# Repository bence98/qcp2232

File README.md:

# QCP2232HV USB-to-Quad UART

## Features

4 TTL UARTs with full Flow Control
* Tx, Rx full duplex
* RTS/CTS (Request-/Clear-to-Send), DTR/DSR (Data Terminal/Set Ready)
* DCD (Data Carrier Detect), RI (Ring Indicator) inputs
* all pins ESD protected
  * full TVS diode protection
  * overcurrent limiting resistors
* see pinout at the end of the section

UART0 and UART1 have RS-232 option
* only Tx/Rx
* separate industrial connector
  * Phoenix MCV 1,5 G-3.81
  * Würth WR-TBL 321

UART3 has selectable TTL voltage (`Vsel`)
* 5V from USB or 3.3V from internal regulator
* UART0-2 are 3.3V

USB Type-B connector
* superior mechanical stability compared to Micro-B
* easier to handle than Mini-B
* more economical to produce than Type-C
* added noise immunity thanks to EMI suppression circuitry
* supports USB suspend mode

16 GPIOs
* 3.3V digital I/O
* all pins ESD protected
  * full TVS diode protection
  * overcurrent limiting resistors
* alternate functions, see table below
  * Tx, Rx LED: blinks on data transfer
  * Tx mode: for half duplex bus drivers eg. RS-485
  * clock: USART bit clock
* configurable via Silicon Labs' toolchain

| GPIO # | UART # | function |
|--------|--------|----------|
|      0 |      0 |   Tx LED |
|      1 |      0 |   Rx LED |
|      2 |      0 |  Tx mode |
|      3 |      0 |    clock |
|      4 |      1 |   Tx LED |
|      5 |      1 |   Rx LED |
|      6 |      1 |  Tx mode |
|      7 |      1 |    clock |
|      8 |      2 |   Tx LED |
|      9 |      2 |   Rx LED |
|     10 |      2 |  Tx mode |
|     11 |      2 |    clock |
|     12 |      3 |   Tx LED |
|     13 |      3 |   Rx LED |
|     14 |      3 |  Tx mode |
|     15 |      3 |    clock |

Pinout (UARTs):

|                | GND | TX  | RX | RTS | CTS | DTR | DSR | DCD | RI |
|----------------|-----|-----|----|-----|-----|-----|-----|-----|----|
| Label on board |     | Tx  | Rx | RS  | CS  | DT  | DS  | CD  | RI |
| Direction      | N/A | Out | In | Out | In  | Out | In  | In  | In |

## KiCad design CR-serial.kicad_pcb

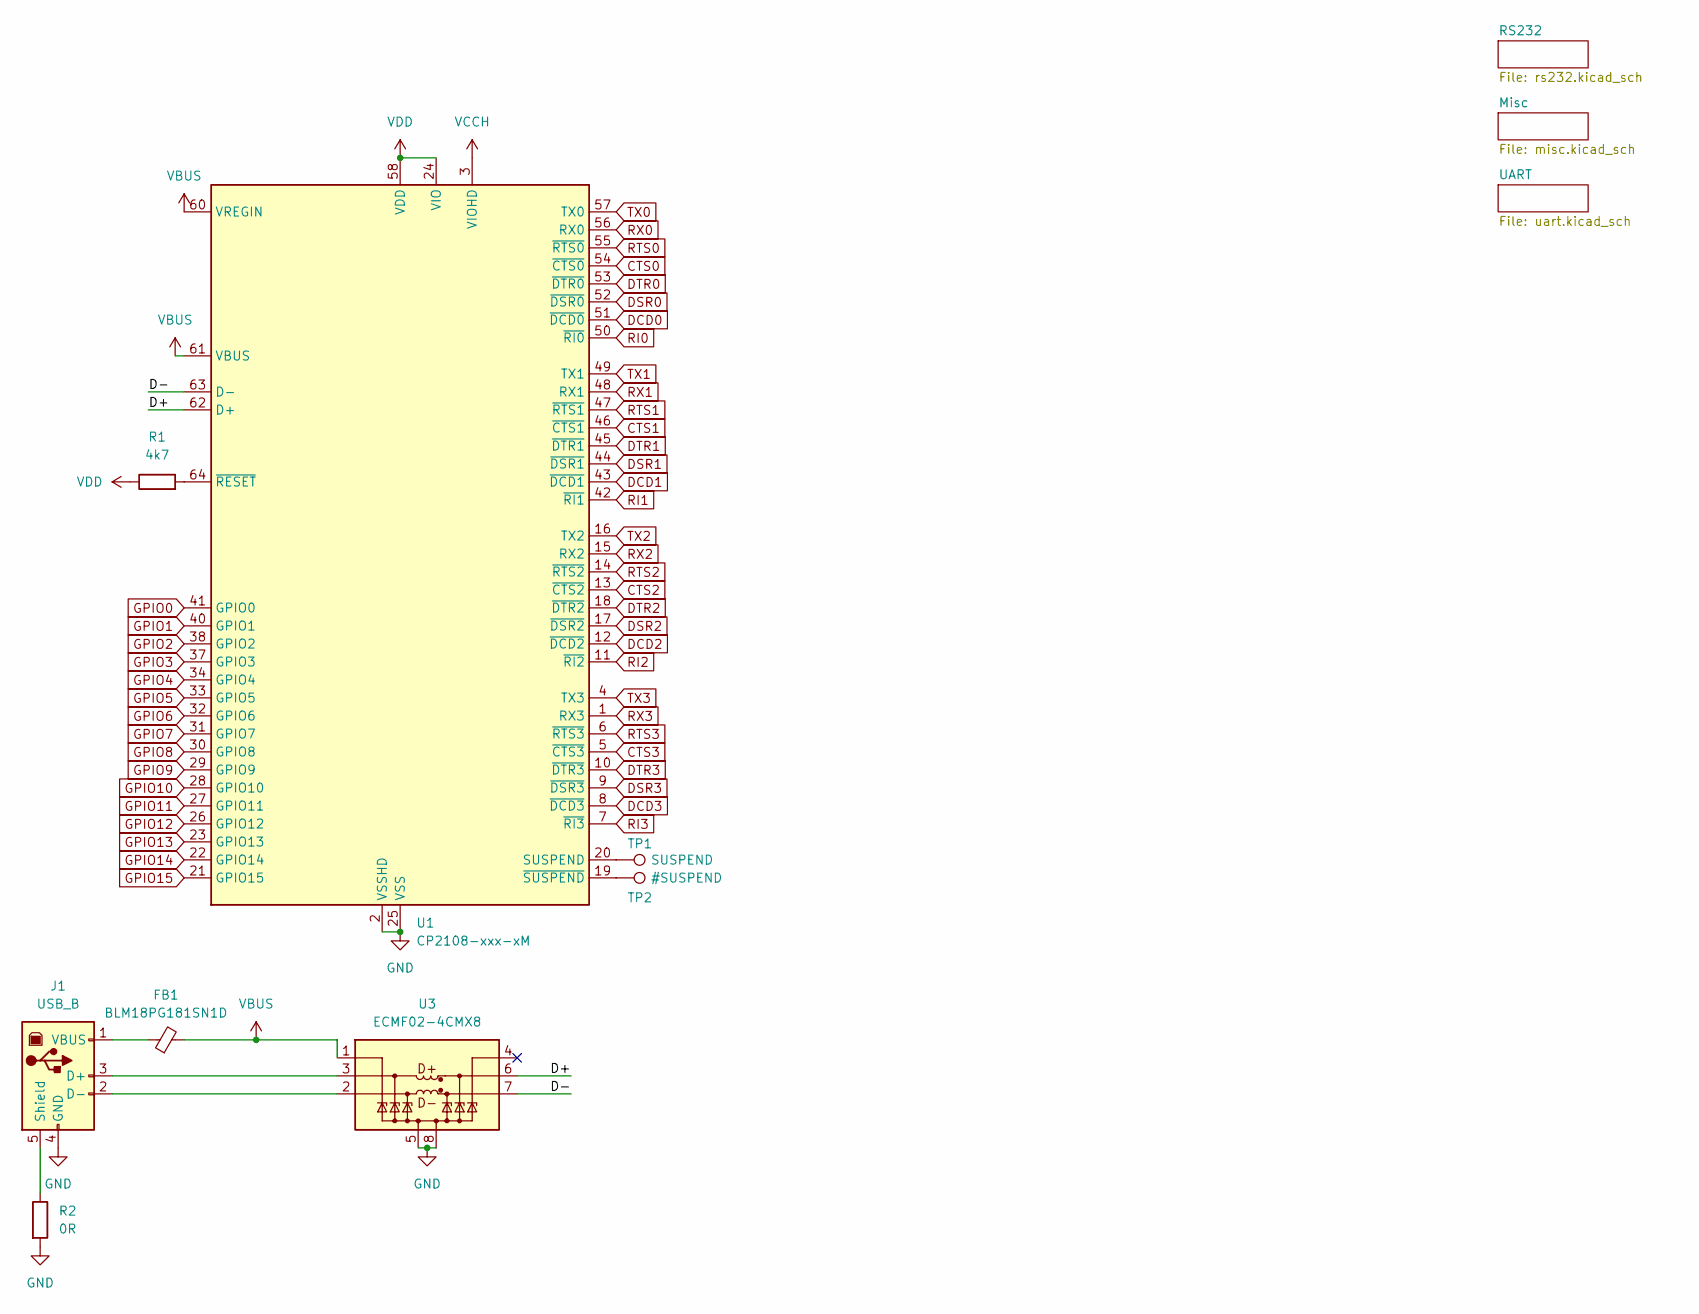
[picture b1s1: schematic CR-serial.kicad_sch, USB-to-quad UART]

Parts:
FB1: BLM18PG181SN1D; L_0603_1608Metric
J1: USB_B; USB_B_OST_USB-B1HSxx_Horizontal
R1: 4k7; R_0603_1608Metric
R2: 0R; R_0603_1608Metric
TP1: SUSPEND; TestPoint_Pad_D1.0mm
TP2: #SUSPEND; TestPoint_Pad_D1.0mm
U1: CP2108-xxx-xM; QFN-64-1EP_9x9mm_P0.5mm_EP4.1x4.1mm
U3: ECMF02-4CMX8; ST_UQFN-8L_1.15x2.45mm_P0.5mm

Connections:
/D+: U1.62 (D+), U3.6 (D+_out)
/D-: U1.63 (D-), U3.7 (D-_out)
CTS0: U1.54 (~CTS0); also elsewhere on the board
CTS1: U1.46 (~CTS1); also elsewhere on the board
CTS2: U1.13 (~CTS2); also elsewhere on the board
CTS3: U1.5 (~CTS3); also elsewhere on the board
DCD0: U1.51 (~DCD0); also elsewhere on the board
DCD1: U1.43 (~DCD1); also elsewhere on the board
DCD2: U1.12 (~DCD2); also elsewhere on the board
DCD3: U1.8 (~DCD3); also elsewhere on the board
DSR0: U1.52 (~DSR0); also elsewhere on the board
DSR1: U1.44 (~DSR1); also elsewhere on the board
DSR2: U1.17 (~DSR2); also elsewhere on the board
DSR3: U1.9 (~DSR3); also elsewhere on the board
DTR0: U1.53 (~DTR0); also elsewhere on the board
DTR1: U1.45 (~DTR1); also elsewhere on the board
DTR2: U1.18 (~DTR2); also elsewhere on the board
DTR3: U1.10 (~DTR3); also elsewhere on the board
GND: J1.4 (GND), R2.2, U1.2 (VSSHD), U1.25 (VSS), U1.59 (VSS), U1.65 (VSS), U3.5 (GND), U3.8 (GND); also elsewhere on the board
GPIO0: U1.41 (GPIO0); also elsewhere on the board
GPIO1: U1.40 (GPIO1); also elsewhere on the board
GPIO2: U1.38 (GPIO2); also elsewhere on the board
GPIO3: U1.37 (GPIO3); also elsewhere on the board
GPIO4: U1.34 (GPIO4); also elsewhere on the board
GPIO5: U1.33 (GPIO5); also elsewhere on the board
GPIO6: U1.32 (GPIO6); also elsewhere on the board
GPIO7: U1.31 (GPIO7); also elsewhere on the board
GPIO8: U1.30 (GPIO8); also elsewhere on the board
GPIO9: U1.29 (GPIO9); also elsewhere on the board
GPIO10: U1.28 (GPIO10); also elsewhere on the board
GPIO11: U1.27 (GPIO11); also elsewhere on the board
GPIO12: U1.26 (GPIO12); also elsewhere on the board
GPIO13: U1.23 (GPIO13); also elsewhere on the board
GPIO14: U1.22 (GPIO14); also elsewhere on the board
GPIO15: U1.21 (GPIO15); also elsewhere on the board
unnamed: J1.3 (D+), U3.3 (D+_in)
unnamed: J1.2 (D-), U3.2 (D-_in)
unnamed: J1.5 (Shield), R2.1
unnamed: FB1.1, J1.1 (VBUS)
unnamed: TP1.1, U1.20 (SUSPEND)
unnamed: R1.2, U1.64 (~RESET)
unnamed: TP2.1, U1.19 (~SUSPEND)
RI0: U1.50 (~RI0); also elsewhere on the board
RI1: U1.42 (~RI1); also elsewhere on the board
RI2: U1.11 (~RI2); also elsewhere on the board
RI3: U1.7 (~RI3); also elsewhere on the board
RTS0: U1.55 (~RTS0); also elsewhere on the board
RTS1: U1.47 (~RTS1); also elsewhere on the board
RTS2: U1.14 (~RTS2); also elsewhere on the board
RTS3: U1.6 (~RTS3); also elsewhere on the board
RX0: U1.56 (RX0); also elsewhere on the board
RX1: U1.48 (RX1); also elsewhere on the board
RX2: U1.15 (RX2); also elsewhere on the board
RX3: U1.1 (RX3); also elsewhere on the board
TX0: U1.57 (TX0); also elsewhere on the board
TX1: U1.49 (TX1); also elsewhere on the board
TX2: U1.16 (TX2); also elsewhere on the board
TX3: U1.4 (TX3); also elsewhere on the board
VBUS: FB1.2, U1.60 (VREGIN), U1.61 (VBUS), U3.1 (VBUS); also elsewhere on the board
VCCH: U1.3 (VIOHD); also elsewhere on the board
VDD: R1.1, U1.24 (VIO), U1.39 (VIO), U1.58 (VDD); also elsewhere on the board

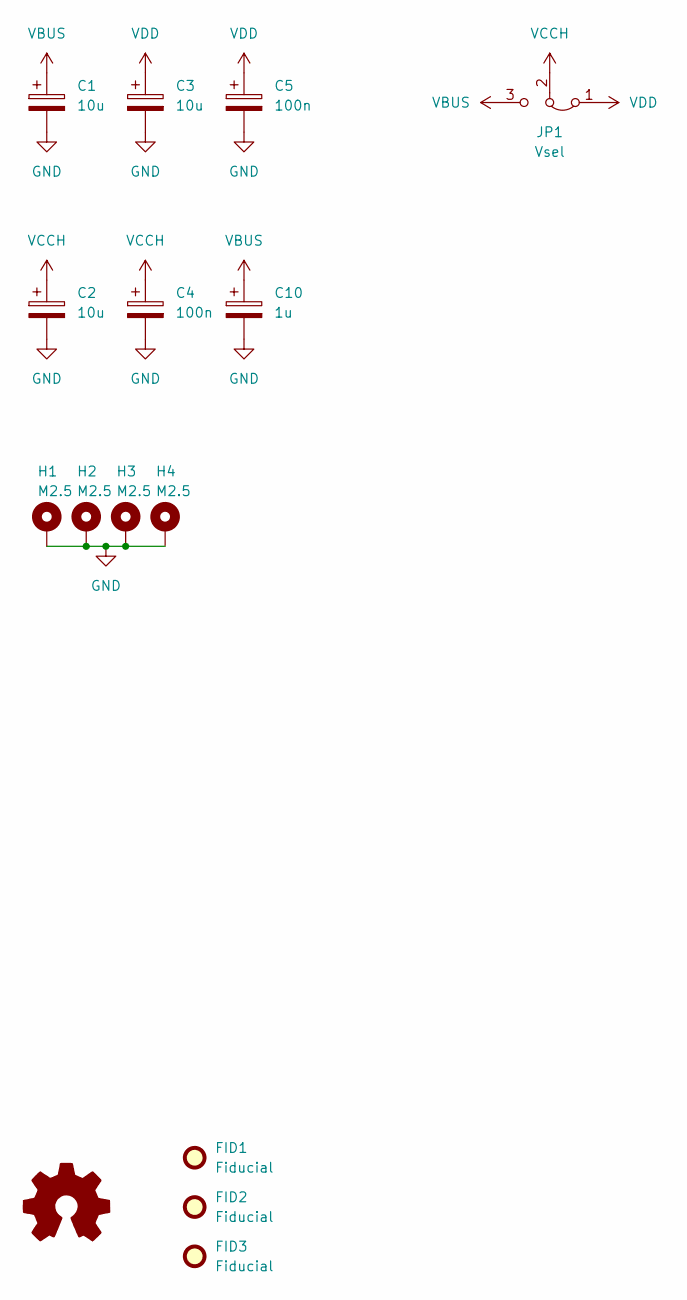
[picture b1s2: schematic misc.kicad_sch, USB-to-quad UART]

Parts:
C1, C2, C3: 10u; C_0603_1608Metric
C4, C5: 100n; C_0603_1608Metric
C10: 1u; C_0603_1608Metric
FID1, FID2, FID3: Fiducial; Fiducial_Cross_0.5mm_Mask2mm
H1, H2, H3, H4: M2.5; MountingHole_2.7mm_M2.5_Pad
JP1: Vsel; SolderJumper-3_P1.3mm_Bridged12_RoundedPad1.0x1.5mm_NumberL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
SYM1: Logo_Open_Hardware_Small; OSHW-Logo2_7.3x6mm_SilkScreen

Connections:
GND: C1.2, C2.2, C3.2, C4.2, C5.2, C10.2, H1.1, H2.1, H3.1, H4.1; also elsewhere on the board
VBUS: C1.1, C10.1, JP1.3 (B); also elsewhere on the board
VCCH: C2.1, C4.1, JP1.2 (C); also elsewhere on the board
VDD: C3.1, C5.1, JP1.1 (A); also elsewhere on the board

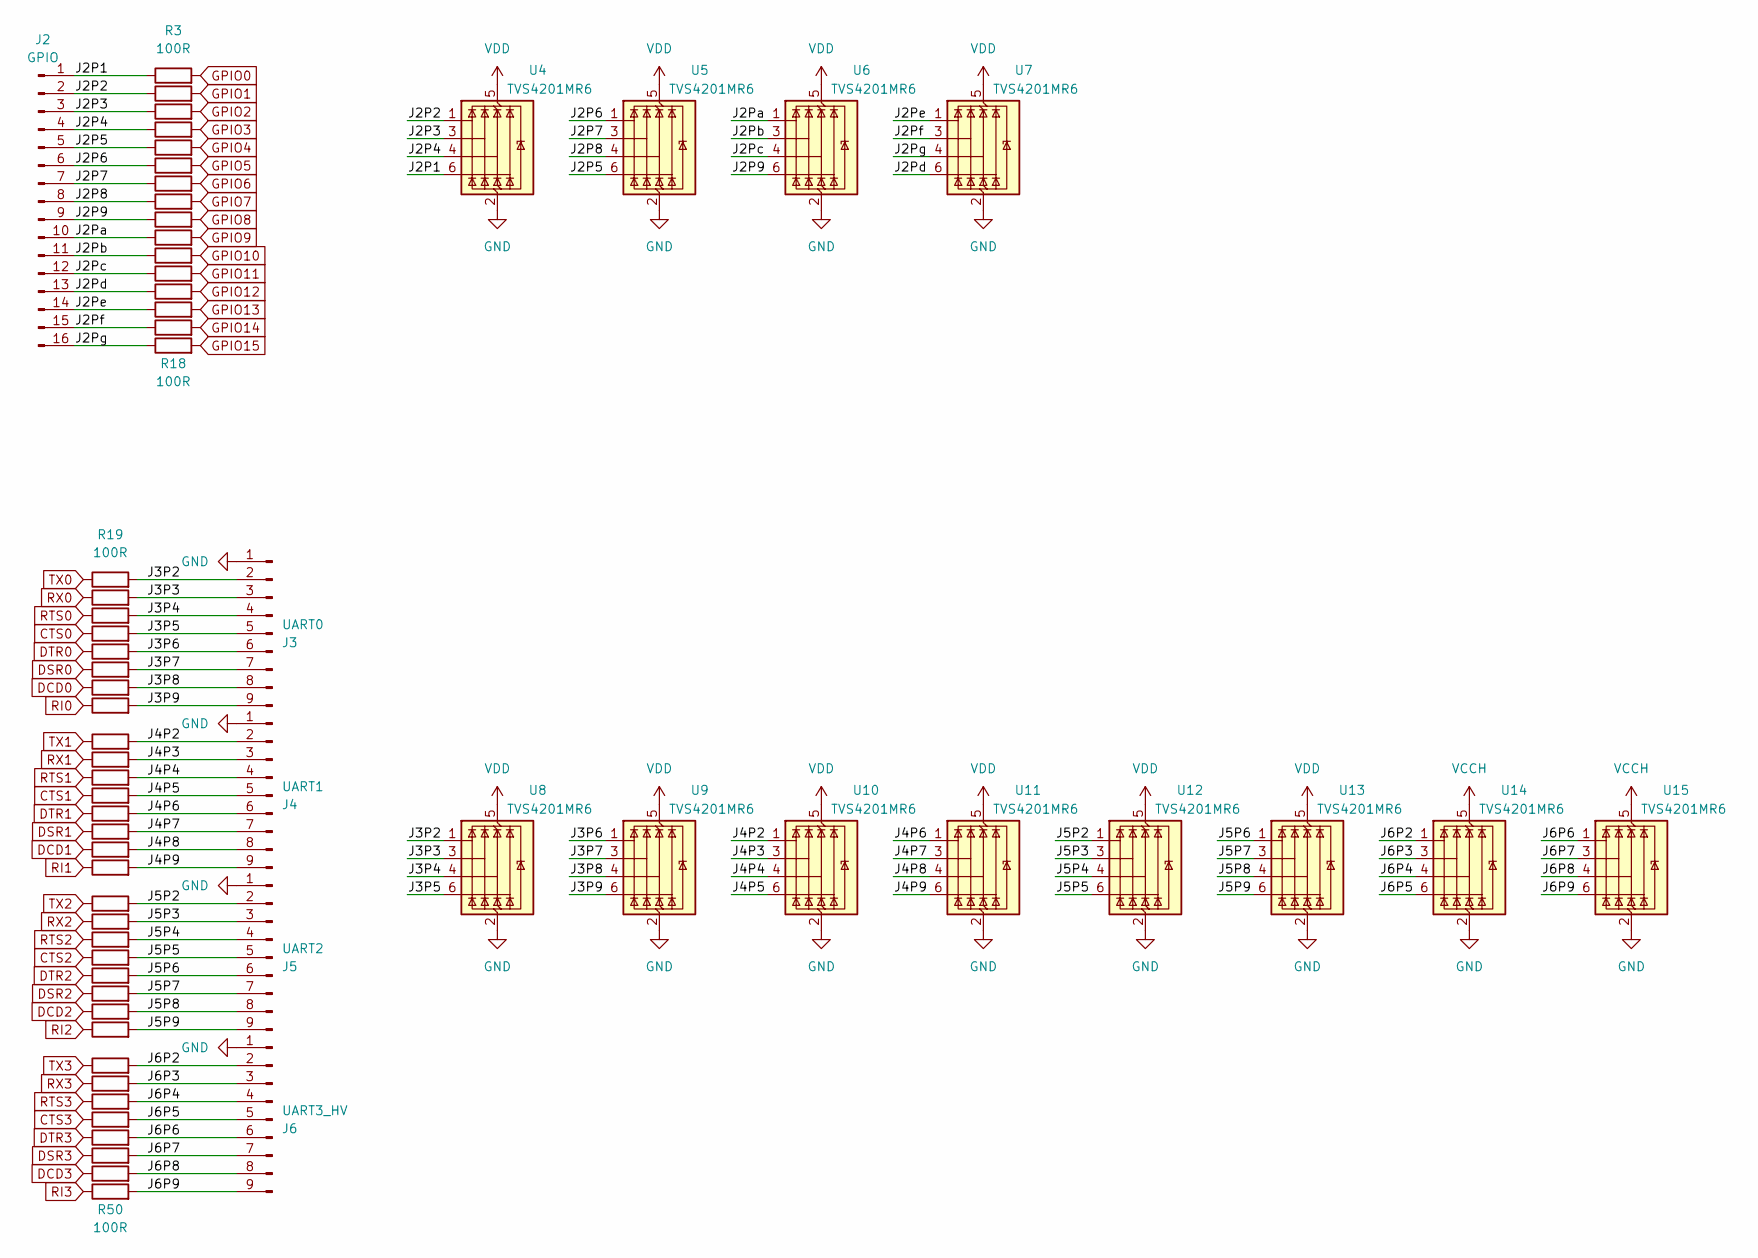
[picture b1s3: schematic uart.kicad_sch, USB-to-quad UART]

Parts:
J2: GPIO; PinHeader_2x08_P2.54mm_Vertical
J3: UART0; PinHeader_1x09_P2.54mm_Vertical
J4: UART1; PinHeader_1x09_P2.54mm_Vertical
J5: UART2; PinHeader_1x09_P2.54mm_Vertical
J6: UART3_HV; PinHeader_1x09_P2.54mm_Vertical
R3, R4, R5, R6, R7, R8, R9, R10, R11, R12, R13, R14, R15, R16, R17, R18, R19, R20, R21, R22, R23, R24, R25, R26, R27, R28, R29, R30, R31, R32, R33, R34, R35, R36, R37, R38, R39, R40, R41, R42, R43, R44, R45, R46, R47, R48, R49, R50: 100R; R_0603_1608Metric
U4, U5, U6, U7, U8, U9, U10, U11, U12, U13, U14, U15: TVS4201MR6; TSOP-6_1.65x3.05mm_P0.95mm

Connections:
/UART/J2P1: J2.1, R3.1, U4.6 (I/O4)
/UART/J2P2: J2.2, R4.1, U4.1 (I/O1)
/UART/J2P3: J2.3, R5.1, U4.3 (I/O2)
/UART/J2P4: J2.4, R6.1, U4.4 (I/O3)
/UART/J2P5: J2.5, R7.1, U5.6 (I/O4)
/UART/J2P6: J2.6, R8.1, U5.1 (I/O1)
/UART/J2P7: J2.7, R9.1, U5.3 (I/O2)
/UART/J2P8: J2.8, R10.1, U5.4 (I/O3)
/UART/J2P9: J2.9, R11.1, U6.6 (I/O4)
/UART/J2Pa: J2.10, R12.1, U6.1 (I/O1)
/UART/J2Pb: J2.11, R13.1, U6.3 (I/O2)
/UART/J2Pc: J2.12, R14.1, U6.4 (I/O3)
/UART/J2Pd: J2.13, R15.1, U7.6 (I/O4)
/UART/J2Pe: J2.14, R16.1, U7.1 (I/O1)
/UART/J2Pf: J2.15, R17.1, U7.3 (I/O2)
/UART/J2Pg: J2.16, R18.1, U7.4 (I/O3)
/UART/J3P2: J3.2, R19.2, U8.1 (I/O1)
/UART/J3P3: J3.3, R20.2, U8.3 (I/O2)
/UART/J3P4: J3.4, R21.2, U8.4 (I/O3)
/UART/J3P5: J3.5, R22.2, U8.6 (I/O4)
/UART/J3P6: J3.6, R23.2, U9.1 (I/O1)
/UART/J3P7: J3.7, R24.2, U9.3 (I/O2)
/UART/J3P8: J3.8, R25.2, U9.4 (I/O3)
/UART/J3P9: J3.9, R26.2, U9.6 (I/O4)
/UART/J4P2: J4.2, R27.2, U10.1 (I/O1)
/UART/J4P3: J4.3, R28.2, U10.3 (I/O2)
/UART/J4P4: J4.4, R29.2, U10.4 (I/O3)
/UART/J4P5: J4.5, R30.2, U10.6 (I/O4)
/UART/J4P6: J4.6, R31.2, U11.1 (I/O1)
/UART/J4P7: J4.7, R32.2, U11.3 (I/O2)
/UART/J4P8: J4.8, R33.2, U11.4 (I/O3)
/UART/J4P9: J4.9, R34.2, U11.6 (I/O4)
/UART/J5P2: J5.2, R35.2, U12.1 (I/O1)
/UART/J5P3: J5.3, R36.2, U12.3 (I/O2)
/UART/J5P4: J5.4, R37.2, U12.4 (I/O3)
/UART/J5P5: J5.5, R38.2, U12.6 (I/O4)
/UART/J5P6: J5.6, R39.2, U13.1 (I/O1)
/UART/J5P7: J5.7, R40.2, U13.3 (I/O2)
/UART/J5P8: J5.8, R41.2, U13.4 (I/O3)
/UART/J5P9: J5.9, R42.2, U13.6 (I/O4)
/UART/J6P2: J6.2, R43.2, U14.1 (I/O1)
/UART/J6P3: J6.3, R44.2, U14.3 (I/O2)
/UART/J6P4: J6.4, R45.2, U14.4 (I/O3)
/UART/J6P5: J6.5, R46.2, U14.6 (I/O4)
/UART/J6P6: J6.6, R47.2, U15.1 (I/O1)
/UART/J6P7: J6.7, R48.2, U15.3 (I/O2)
/UART/J6P8: J6.8, R49.2, U15.4 (I/O3)
/UART/J6P9: J6.9, R50.2, U15.6 (I/O4)
CTS0: R22.1; also elsewhere on the board
CTS1: R30.1; also elsewhere on the board
CTS2: R38.1; also elsewhere on the board
CTS3: R46.1; also elsewhere on the board
DCD0: R25.1; also elsewhere on the board
DCD1: R33.1; also elsewhere on the board
DCD2: R41.1; also elsewhere on the board
DCD3: R49.1; also elsewhere on the board
DSR0: R24.1; also elsewhere on the board
DSR1: R32.1; also elsewhere on the board
DSR2: R40.1; also elsewhere on the board
DSR3: R48.1; also elsewhere on the board
DTR0: R23.1; also elsewhere on the board
DTR1: R31.1; also elsewhere on the board
DTR2: R39.1; also elsewhere on the board
DTR3: R47.1; also elsewhere on the board
GND: J3.1, J4.1, J5.1, J6.1, U4.2 (GND), U5.2 (GND), U6.2 (GND), U7.2 (GND), U8.2 (GND), U9.2 (GND), U10.2 (GND), U11.2 (GND), U12.2 (GND), U13.2 (GND), U14.2 (GND), U15.2 (GND); also elsewhere on the board
GPIO0: R3.2; also elsewhere on the board
GPIO1: R4.2; also elsewhere on the board
GPIO2: R5.2; also elsewhere on the board
GPIO3: R6.2; also elsewhere on the board
GPIO4: R7.2; also elsewhere on the board
GPIO5: R8.2; also elsewhere on the board
GPIO6: R9.2; also elsewhere on the board
GPIO7: R10.2; also elsewhere on the board
GPIO8: R11.2; also elsewhere on the board
GPIO9: R12.2; also elsewhere on the board
GPIO10: R13.2; also elsewhere on the board
GPIO11: R14.2; also elsewhere on the board
GPIO12: R15.2; also elsewhere on the board
GPIO13: R16.2; also elsewhere on the board
GPIO14: R17.2; also elsewhere on the board
GPIO15: R18.2; also elsewhere on the board
RI0: R26.1; also elsewhere on the board
RI1: R34.1; also elsewhere on the board
RI2: R42.1; also elsewhere on the board
RI3: R50.1; also elsewhere on the board
RTS0: R21.1; also elsewhere on the board
RTS1: R29.1; also elsewhere on the board
RTS2: R37.1; also elsewhere on the board
RTS3: R45.1; also elsewhere on the board
RX0: R20.1; also elsewhere on the board
RX1: R28.1; also elsewhere on the board
RX2: R36.1; also elsewhere on the board
RX3: R44.1; also elsewhere on the board
TX0: R19.1; also elsewhere on the board
TX1: R27.1; also elsewhere on the board
TX2: R35.1; also elsewhere on the board
TX3: R43.1; also elsewhere on the board
VCCH: U14.5 (VBUS), U15.5 (VBUS); also elsewhere on the board
VDD: U4.5 (VBUS), U5.5 (VBUS), U6.5 (VBUS), U7.5 (VBUS), U8.5 (VBUS), U9.5 (VBUS), U10.5 (VBUS), U11.5 (VBUS), U12.5 (VBUS), U13.5 (VBUS); also elsewhere on the board

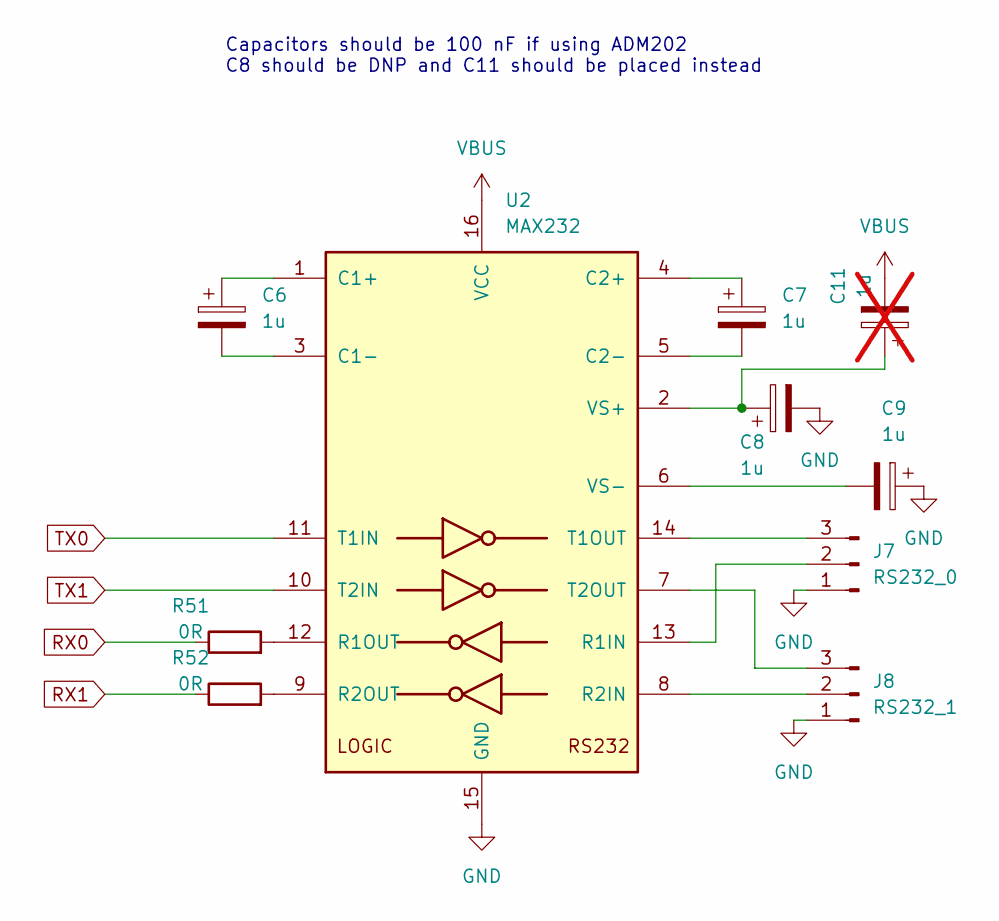
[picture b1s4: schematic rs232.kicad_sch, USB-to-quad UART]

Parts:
C6, C7, C8, C9: 1u; C_0603_1608Metric
C11: 1u; C_0603_1608Metric; not fitted
J7: RS232_0; PhoenixContact_MCV_1,5_3-G-3.81_1x03_P3.81mm_Vertical
J8: RS232_1; PhoenixContact_MCV_1,5_3-G-3.81_1x03_P3.81mm_Vertical
R51, R52: 0R; R_0603_1608Metric
U2: MAX232; SOIC-16_3.9x9.9mm_P1.27mm

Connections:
GND: C8.2, C9.1, J7.1, J8.1, U2.15 (GND); also elsewhere on the board
unnamed: J7.2, U2.13 (R1IN)
unnamed: J7.3, U2.14 (T1OUT)
unnamed: J8.2, U2.8 (R2IN)
unnamed: J8.3, U2.7 (T2OUT)
unnamed: C6.1, U2.1 (C1+)
unnamed: C6.2, U2.3 (C1-)
unnamed: C7.1, U2.4 (C2+)
unnamed: C7.2, U2.5 (C2-)
unnamed: R51.2, U2.12 (R1OUT)
unnamed: R52.2, U2.9 (R2OUT)
unnamed: C8.1, C11.1, U2.2 (VS+)
unnamed: C9.2, U2.6 (VS-)
RX0: R51.1; also elsewhere on the board
RX1: R52.1; also elsewhere on the board
TX0: U2.11 (T1IN); also elsewhere on the board
TX1: U2.10 (T2IN); also elsewhere on the board
VBUS: C11.2, U2.16 (VCC); also elsewhere on the board

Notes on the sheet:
Capacitors should be 100 nF if using ADM202 C8 should be DNP and C11 should be placed instead

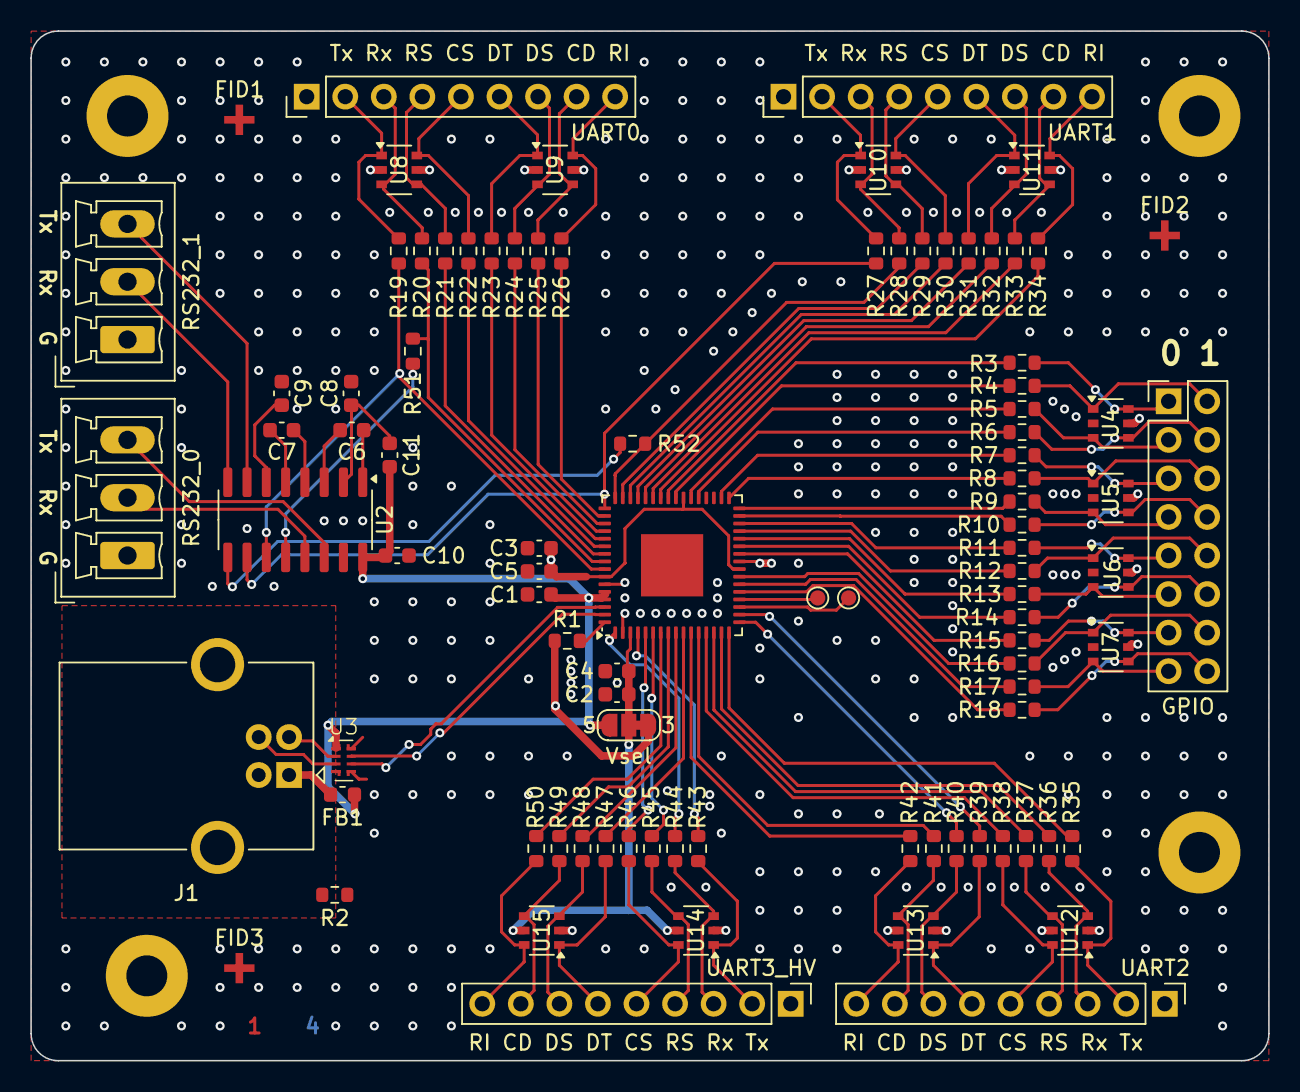
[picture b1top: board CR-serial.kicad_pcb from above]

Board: 4 copper layers, 81.5 x 67.8 mm, 98 parts (1 on the bottom side), 121 nets.

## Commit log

2024-08-02 First revision: CP2108-based, fully routed
2024-08-05 Add .gitignore
2024-08-05 Make GPIO header double-row
2024-08-05 Move UART1 header to the edge of the board
2024-08-05 Hide unnecessary designators from F.Silk
2024-08-09 Move UART0 connector around
2024-08-09 Extend board, move UART2-3 around
    (Areas unfilled...)
2024-08-13 Change RS232 connectors
    Zones filled again
2024-08-16 Add silkscreen markings
    `--patience` is recommended for viewing
2024-08-26 Refactor UARTs: move GND next to TX/RX
2024-08-27 Add 0Rs on all CP2108 outputs
    `--patience` is recommended
2024-08-27 Change USB connector to USB-B
    `--patience` is recommended
2024-08-27 Change passives to 0603 size
2024-08-28 Change USB protection: add ECMF02-4CMX8
2024-08-29 UARTs: Rework ESD protection, use individual Rs, add TVS
2024-08-29 Refactor: split out RS-232 driver and misc components
    (e.g. bus capacitors, mounting holes)
2024-08-30 Export common fields to all sheets
2024-08-30 WIP: Refactor: split out UART headers to a new page
2024-08-30 Refactor: split out UART headers to a new page
2024-08-30 More and bigger screw holes
2024-08-30 Bigger caps
2024-08-30 Renumber TVS diodes' legs to ease PCB routing
2024-09-03 New board
    * 4 layers: internal VDD, GND plane
    * connectors on board edge
    * MAX232 on top
    * product name on bottom
    * lots of (nested) groups
    * and of course, the schematic changes
2024-09-04 More silkscreen work
2024-09-04 Re-add OSHW logo, add GH URL, move caps
2024-09-04 Round off corners
2024-09-04 Stitch vias
    A lot... of... stitch vias...
2024-09-05 PCB: add title
2024-09-05 Add README
2024-09-06 Library: Fix default footprint, add descriptions
2024-09-10 Group GND vias
    UUID list generated with:
    ```Bash
    git show 7479980e2907 --patience | grep -e "+.*uuid" | cut -d\" -f2
    ```
2024-09-10 More GND vias
2024-09-10 PCB: Add layer indicator
2024-09-10 Add one more capacitor to VBUS
2024-09-12 Add option for ADM202
2024-09-23 Change `.1u` to `100n` for clarity
2024-09-23 Fix ferrite bead footprint
2024-09-23 Update PCB: fix ferrite and 100nF capacitors
2024-09-24 Add RS232 RX enable for more flexibility
2024-09-30 PCB: Add RS232 RX enable resistors, unfill zones
2024-09-30 Add fiducials
2025-03-12 Case: Add STL and F3Z files of the first printed case
    Designed with Fusion 360
